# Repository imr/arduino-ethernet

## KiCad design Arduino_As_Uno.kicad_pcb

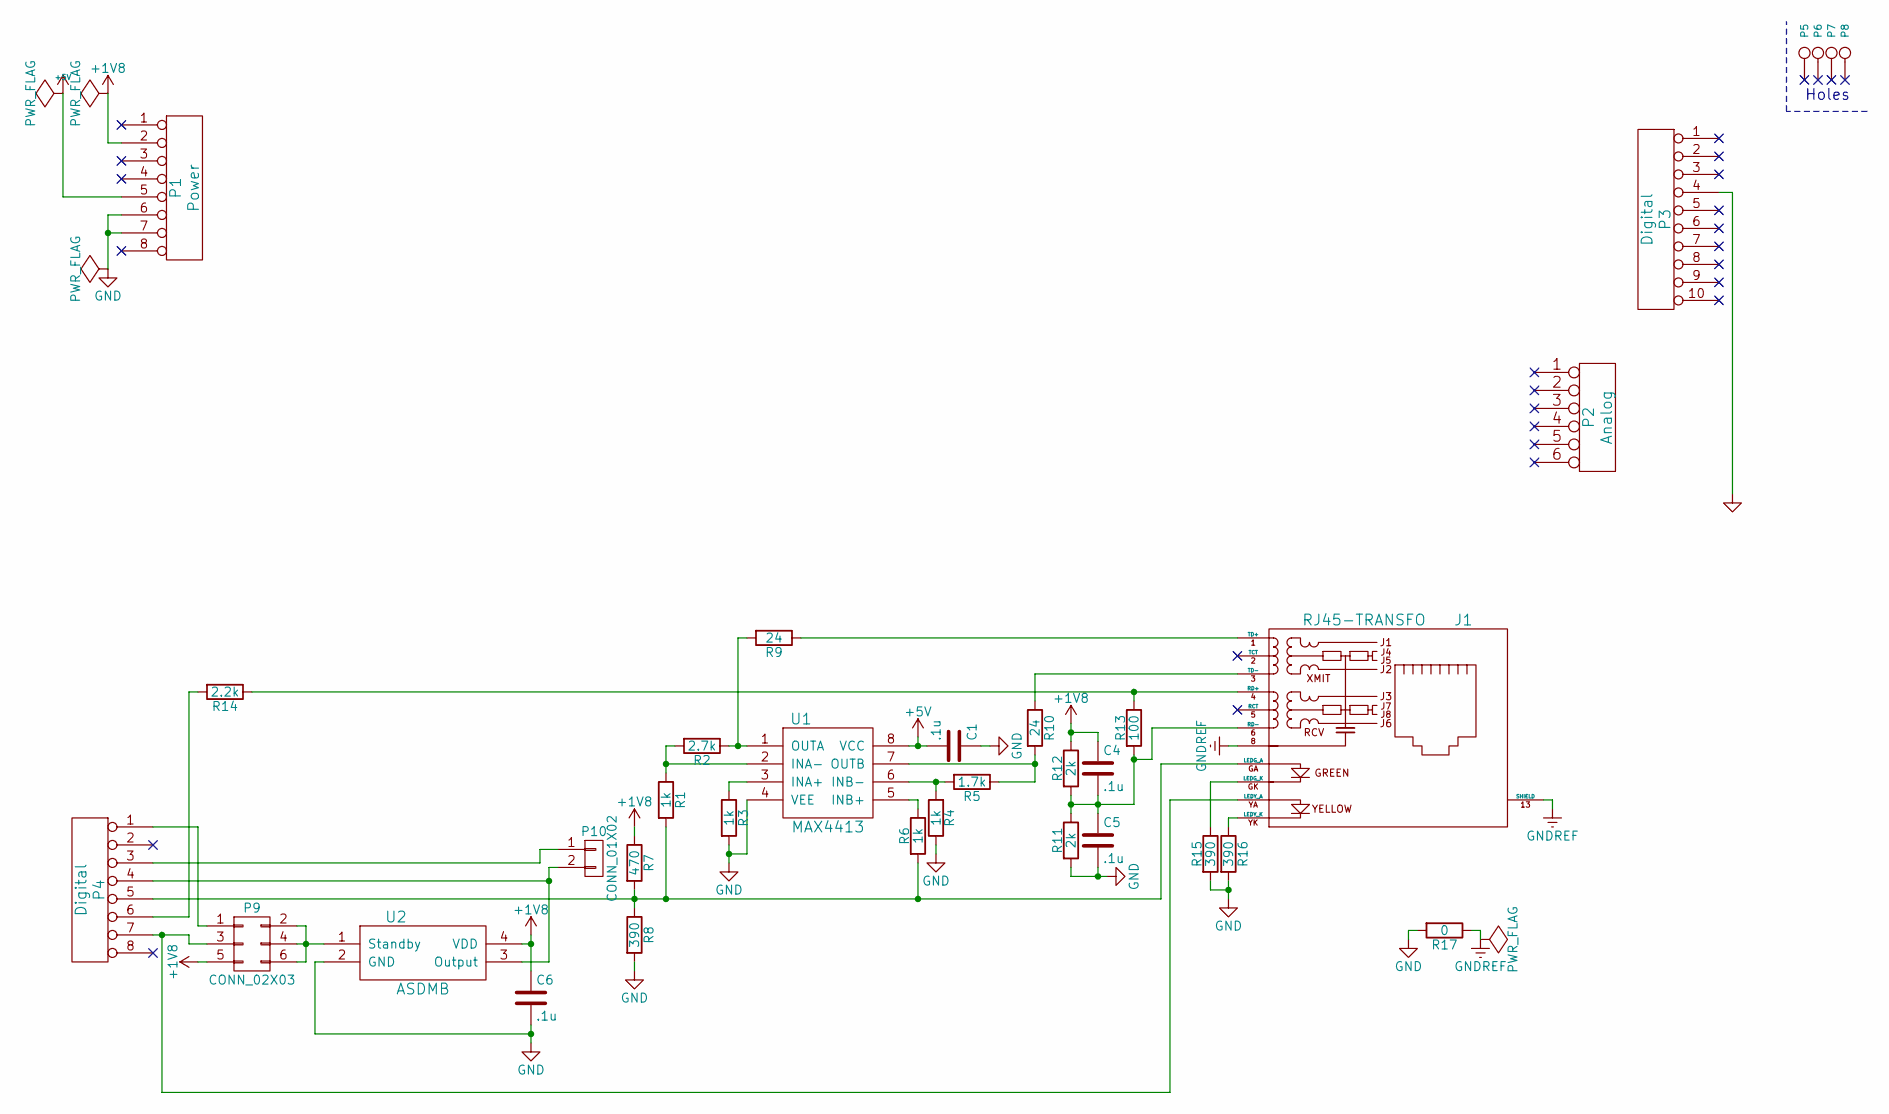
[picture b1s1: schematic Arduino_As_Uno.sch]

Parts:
C1, C4, C5, C6: .1u; C_0805_HandSoldering
J1: RJ45-TRANSFO; RJ45_TRANSFO
P1: Power; Socket_Strip_Arduino_1x08
P2: Analog; Socket_Strip_Arduino_1x06
P3: Digital; Socket_Strip_Arduino_1x10
P4: Digital; Socket_Strip_Arduino_1x08
P5, P6, P7, P8: CONN_1; Arduino_1pin
P9: CONN_02X03; Pin_Header_Straight_2x03
P10: CONN_01X02; Pin_Header_Straight_1x02
R1, R3, R4, R6: 1k; R_0805_HandSoldering
R2: 2.7k; R_0805_HandSoldering
R5: 1.7k; R_0805_HandSoldering
R7: 470; R_0805_HandSoldering
R8, R15, R16: 390; R_0805_HandSoldering
R9, R10: 24; R_2512_HandSoldering
R11, R12: 2k; R_0805_HandSoldering
R13: 100; R_2512_HandSoldering
R14: 2.2k; R_0805_HandSoldering
R17: 0; R_2512_HandSoldering
U1: MAX4413; SOT-23-8
U2: ASDMB

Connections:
+1V8: C4.1, C6.1, P1.2, P9.5, R7.1, R12.1, U2.4 (VDD)
+5V: C1.2, P1.5, U1.8 (VCC)
GND: C1.1, C5.2, C6.2, P1.6, P1.7, P3.4, R3.2, R4.1, R8.2, R11.2, R15.2, R16.2, R17.2, U1.4 (VEE), U2.2 (GND)
GNDREF: J1.8, J1.13 (SHIELD), R17.1
unnamed: C4.2, C5.1, J1.6 (RD-), R11.1, R12.2, R13.2
unnamed: J1.1 (TD+), R9.1
unnamed: J1.3 (TD-), R10.1
unnamed: J1.4 (RD+), R13.1, R14.1
unnamed: J1.GA (LEDG_A), P4.5, R1.2, R6.2, R7.2, R8.1
unnamed: J1.GK (LEDG_K), R15.1
unnamed: J1.YA (LEDY_A), P4.7, P9.3
unnamed: J1.YK (LEDY_K), R16.1
unnamed: P4.1, P9.1
unnamed: P4.6, R14.2
unnamed: P9.2, P9.4, P9.6, U2.1 (Standby)
unnamed: P4.3, P10.1
unnamed: P4.4, P10.2, U2.3 (Output)
unnamed: R1.1, R2.2, U1.2 (INA-)
unnamed: R2.1, R9.2, U1.1 (OUTA)
unnamed: R3.1, U1.3 (INA+)
unnamed: R4.2, R5.2, U1.6 (INB-)
unnamed: R6.1, U1.5 (INB+)
unnamed: R5.1, R10.2, U1.7 (OUTB)

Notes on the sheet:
Holes

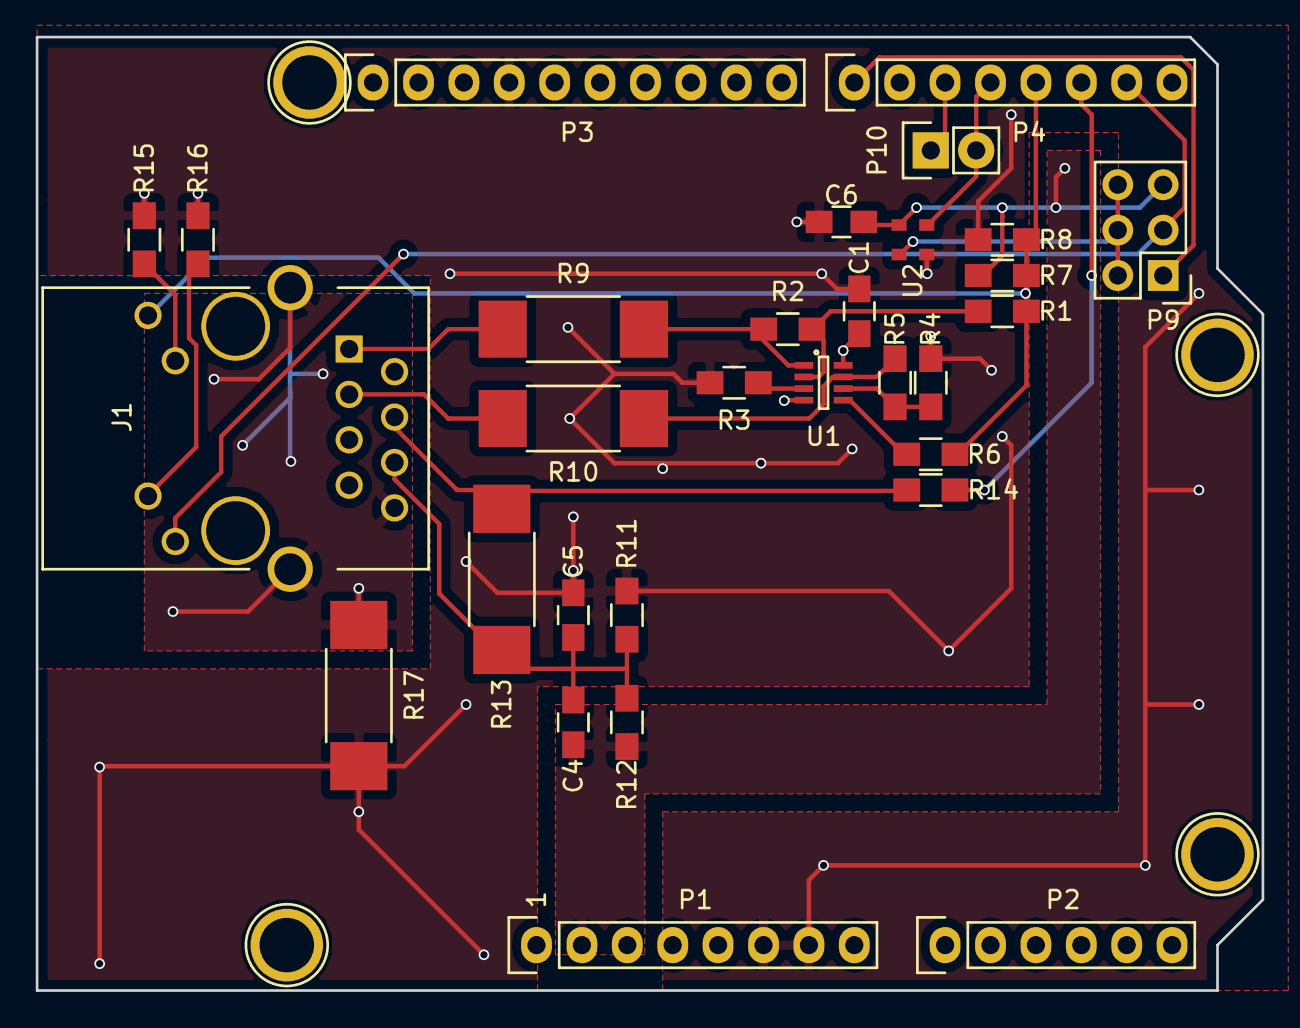
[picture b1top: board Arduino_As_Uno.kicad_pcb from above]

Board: 2 copper layers, 68.6 x 53.3 mm, 34 parts (0 on the bottom side), 23 nets.

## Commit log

2015-10-09 Initial import of template.
2015-10-09 Add gitignore file.
2015-10-10 First design sent out.
